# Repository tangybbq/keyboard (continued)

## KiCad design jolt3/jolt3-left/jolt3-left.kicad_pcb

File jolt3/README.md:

# The Jolt 3

The Jolt 2, with the varying-elevation design has turned out to be a rather nice keyboard to use.
However there are some challenges:

- Even with sockets, assembling all of the key risers is quite time consuming.  This makes it more
  challenging to experiment with the rest of the electronics.
- With more circuitry on the main board, the left/right distinction greatly increases the work to
  try a new design.

As such, the main goal of the Jolt 3 is to modularize the board design.  This is similar to using
existing rp2040 modules in the design, but in this case, the mezzanine board is my design instead,
with the following changes:

- Larger available area.  This allows me to put more on the board.
- Always have a debug headers.  The plethora of small boards that don't bother with debug headers is
  baffling to me.  I understand a lot of people are doing python, but this makes the board almost
  entirely useless for any serious development.

In order to make this board able to be used on either side of the keyboard, we'll need to avoid any
connectors that vary from side to side, notably the rj-45 (or whatever jack I decide on).  Now might
be a good time to try a different connector.  USB-C would work well for this, but it seems to be
hard to find thin USB-C cables.  I don't want 240W, I want a thin cable.  The old Apple cable is
really nice, but is getting harder and harder to find.  Another option is RJ-9.  The cables aren't
quite as available (and tend to be curly), but this might be a nice compromise.

Another thought, since I now have a tented stand, is to put the rj45 on the bottom side of the
board, and cut a notch for it.

It is fine to have the USB and debug header on the small board.

Sockets are going to be nice.  Regular pin header sockets are fine, but do lift the board up quite a
bit.  It still might end up being the best approach, as narrower pitch are harder to find.

This design should make some number of pins available in standard places:

- GPIOs for row and column.  4+6 is adequate for any of my current designs.  A two-row version with
  a single CPU would need 5+6, so 11 pins for this seems fine.
- Pins for the RJ-45?  If this is underneath, it gives more space.
- Battery.  The base board should be designed to allow a battery underneath.  The lines will just
  run directly to the small board.

## Dimensions

If we put the RJ-45 underneath, this gives us 41mm across by 39mm high.  It might make more sense to
just have the board be square at 40x40mm.

For a two-row design, this space could still be available.  It is unclear to me where my future
desire for 2-row will go (it depends on whether I become fully comfortable with steno+taipo).

## Design

The main boards will be jolt3-left, and jolt3-right, with the same connector on each.

- Supports the 7 risers in the same positioning and connection as the jolt2.
- Has a 40x40mm area for a mezzanine board.
- Defines a pinout for connections between the boards.  There are 20 pins needed, plus whatever is
  needed for extra grounding. A single row is likely to be fine.r
- Decide on the particular mezzanine connector to use.  It might make sense to have on one side with
  standoffs on the other sides.

The smallest M-2 size is 22x42, which would fit (but give half the available area.

I've ended up going for the [DF40C](https://www.hirose.com/product/p/CL0684-4010-9-51#) series of
connectors, 30 pin with a 3mm board spacing.  I could probably do 2mm, but the pins on the RJ-45 are
fairly long, and 3mm avoids the need to trim.  I'll use 3 1mm thick nylon washers for each standoff.

Rev A implements the following:

- jolt3-left: The left side.  The only components are the holes to mount the risers, the RJ-45, a
  place to mount the 2AA battery holder, and two pull up resistors for I2C.
- jolt3-right: The same as left, with minor changes: no pullups on I2C, Tx and Rx on the serial
  lines are swapped.
- jolt3-mez2040: The rp2040 circuitry on the mezzanine board.  I ended up with 38x38mm, to bring the
  mounting holes in enough on the main board to clear the stand.  The rp2040 is rotated 90 degrees
  to better route gpios to the connector (moves the crystal out of the way).
- Use the same riser boards "jolt2-verts" from the Jolt2.

The biggest change from previous designs is moving away from the Arm Cortex-M debug header to the
6-pin [Tag Connect](https://www.tag-connect.com/).  This requires no components on the board, just
some holes and pads, taking about the same area as the Cortex-M connector.  There is a smaller one,
but for these prototypes, the definitive connection seems better.  The cable is about $45 and should
last a long time.

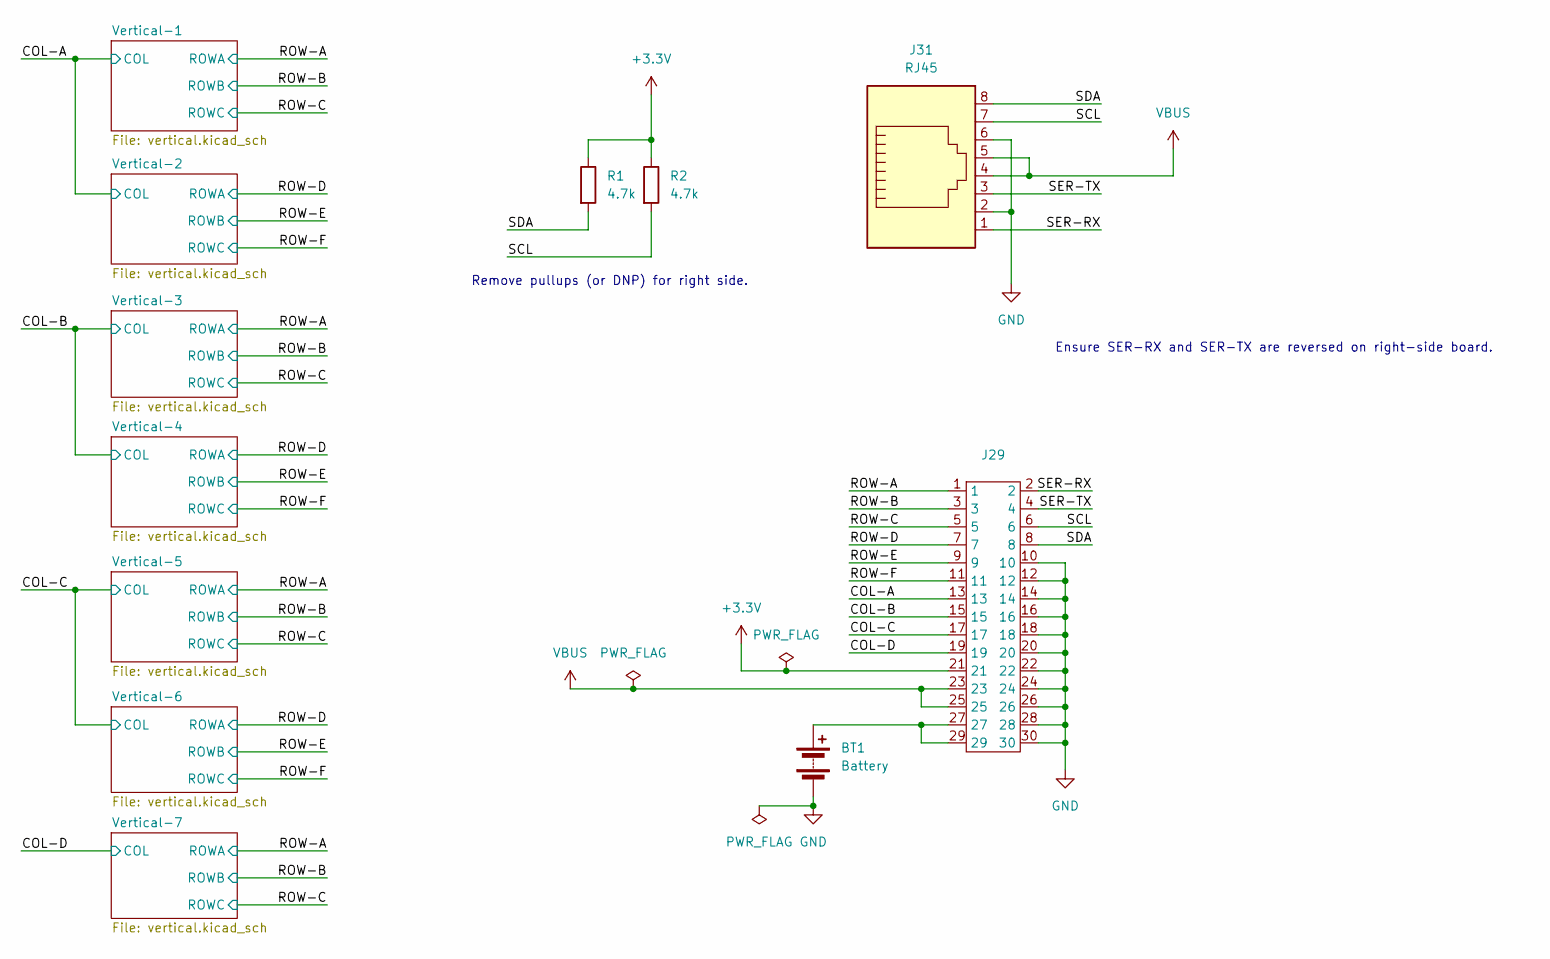
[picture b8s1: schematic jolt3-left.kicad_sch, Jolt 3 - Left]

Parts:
BT1: Battery; BAT-2xAA-SHELL-CASE-BOX
J29: df40c-2_0-30P-0_4v
J31: RJ45; RJ45_Amphenol_54602-x08_Horizontal
R1, R2: 4.7k; R_0603_1608Metric_Pad0.98x0.95mm_HandSolder

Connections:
+3.3V: J29.21, R1.1, R2.1
/COL-A: J29.13; also elsewhere on the board
/COL-B: J29.15; also elsewhere on the board
/COL-C: J29.17; also elsewhere on the board
/COL-D: J29.19; also elsewhere on the board
/ROW-A: J29.1; also elsewhere on the board
/ROW-B: J29.3; also elsewhere on the board
/ROW-C: J29.5; also elsewhere on the board
/ROW-D: J29.7; also elsewhere on the board
/ROW-E: J29.9; also elsewhere on the board
/ROW-F: J29.11; also elsewhere on the board
/SCL: J29.6, J31.7, R2.2
/SDA: J29.8, J31.8, R1.2
/SER-RX: J29.2, J31.1
/SER-TX: J29.4, J31.3
GND: BT1.2 (-), J29.10, J29.12, J29.14, J29.16, J29.18, J29.20, J29.22, J29.24, J29.26, J29.28, J29.30, J31.2, J31.6
unnamed: BT1.1 (+), J29.27, J29.29
VBUS: J29.23, J29.25, J31.4, J31.5

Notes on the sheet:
Ensure SER-RX and SER-TX are reversed on right-side board.
Remove pullups (or DNP) for right side.

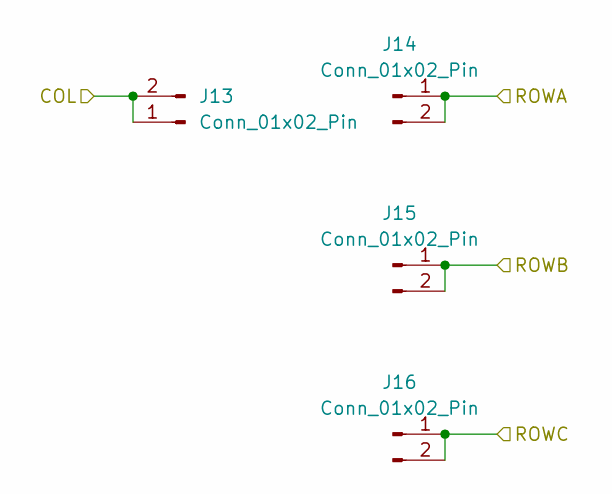
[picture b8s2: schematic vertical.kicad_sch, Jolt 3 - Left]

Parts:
J13, J14, J15, J16: Conn_01x02_Pin; PinHeader_1x02_P2.54mm_Vertical

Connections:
/COL-B: J13.1, J13.2; also elsewhere on the board
/ROW-D: J14.1, J14.2; also elsewhere on the board
/ROW-E: J15.1, J15.2; also elsewhere on the board
/ROW-F: J16.1, J16.2; also elsewhere on the board

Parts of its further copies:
J1, J2, J3, J4, J5, J6, J7, J8, J9, J10, J11, J12, J17, J18, J19, J20, J21, J22, J23, J24, J25, J26, J27, J28: Conn_01x02_Pin; PinHeader_1x02_P2.54mm_Vertical

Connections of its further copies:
/COL-A: J1.1, J1.2, J5.1, J5.2; also elsewhere on the board
/COL-B: J9.1, J9.2; also elsewhere on the board
/COL-C: J17.1, J17.2, J21.1, J21.2; also elsewhere on the board
/COL-D: J25.1, J25.2; also elsewhere on the board
/ROW-A: J2.1, J2.2, J10.1, J10.2, J18.1, J18.2, J26.1, J26.2; also elsewhere on the board
/ROW-B: J3.1, J3.2, J11.1, J11.2, J19.1, J19.2, J27.1, J27.2; also elsewhere on the board
/ROW-C: J4.1, J4.2, J12.1, J12.2, J20.1, J20.2, J28.1, J28.2; also elsewhere on the board
/ROW-D: J6.1, J6.2, J22.1, J22.2; also elsewhere on the board
/ROW-E: J7.1, J7.2, J23.1, J23.2; also elsewhere on the board
/ROW-F: J8.1, J8.2, J24.1, J24.2; also elsewhere on the board

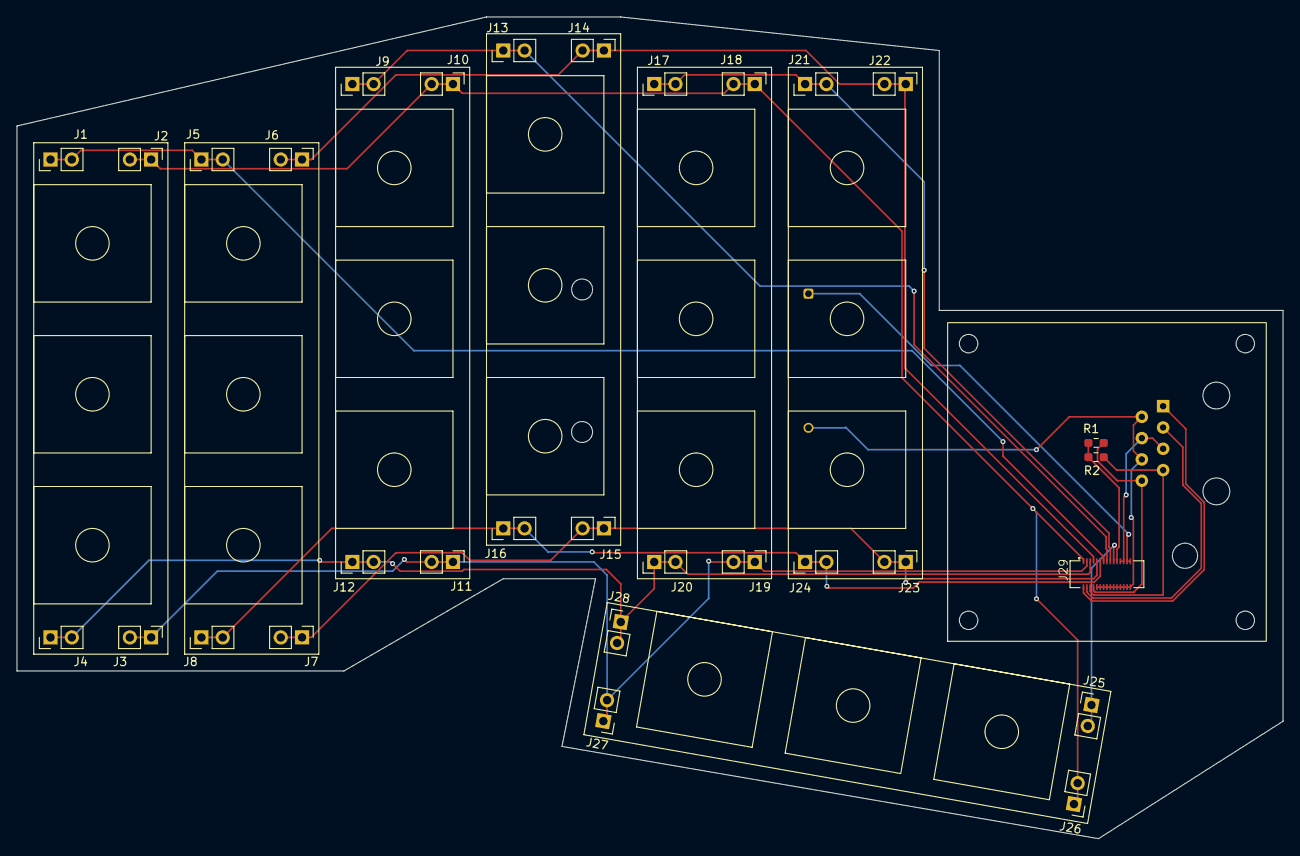
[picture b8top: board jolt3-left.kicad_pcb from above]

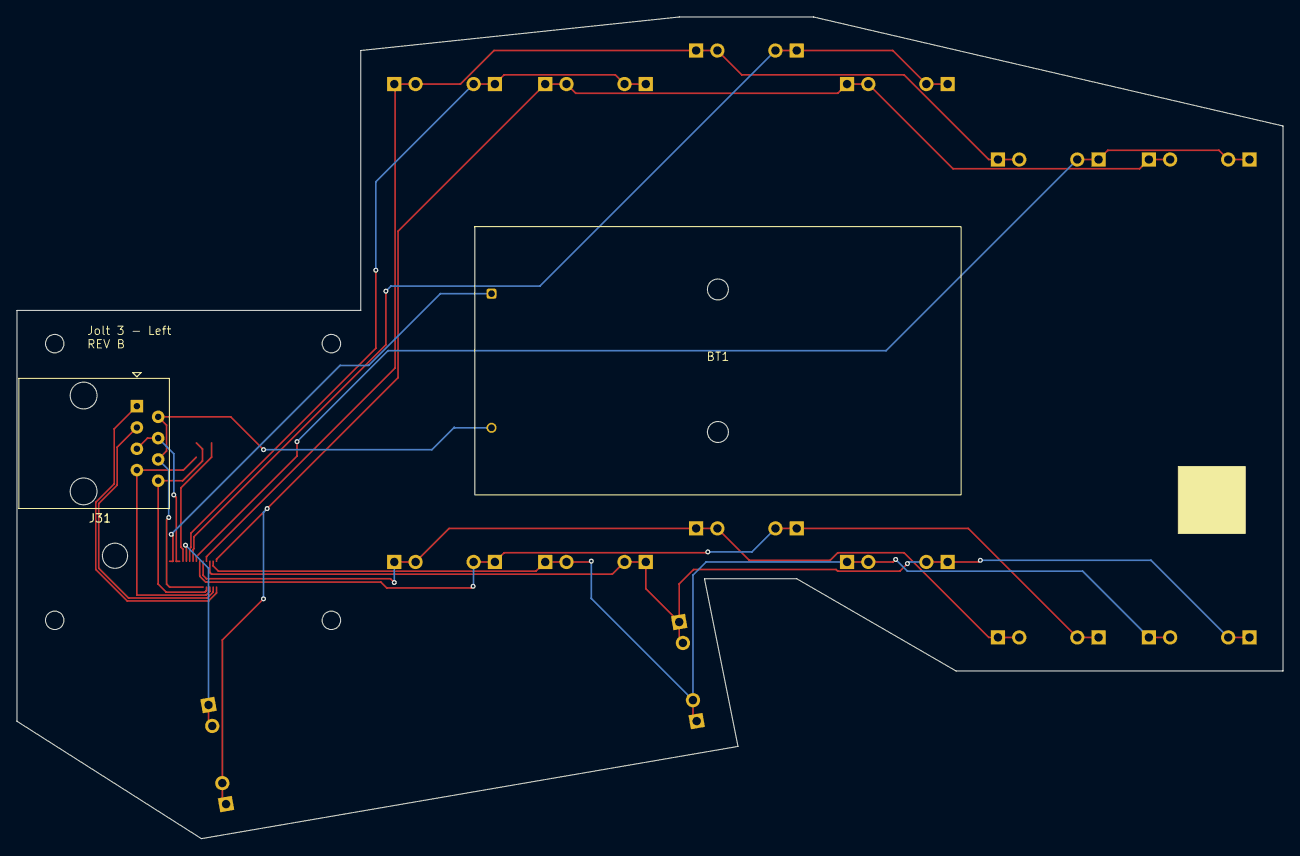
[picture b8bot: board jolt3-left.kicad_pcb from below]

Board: 2 copper layers, 151.0 x 98.0 mm, 33 parts (2 on the bottom side), 18 nets.

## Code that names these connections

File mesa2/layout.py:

#!/usr/bin/env python3
"""mesa2 key layout, derived from hand-scan-1.

Method:
  1. Mirror the right hand about the axis midway between the two hand centroids.
  2. Average it with the left hand, mark for mark. That is the "average of my
     measurements" and it forces a symmetric board; the unibody angle survives
     as the average of the two hands' rotations.
  3. Each finger column: centre = the rest mark (m2), axis = principal direction
     of its three marks, two keys at +/- rock/2 along that axis.
  4. Thumbs: two keys on the measured arc, centred on it, caps tangent.
  5. Emit the averaged hand and its mirror = 20 keys.

Frame is the measurement sheet's: +X right, +Y toward you.
"""
import math, json

ROCK = 17.0          # row pitch, fixed by the caps (16.5 + 0.5)
THUMB_PITCH = 18.0   # thumb pair separation along the arc

MARKS = {
 'L': {'pinky':  [(15.53,30.50),(29.27,35.07),(32.66,38.48)],
       'ring':   [(55.32,20.48),(55.68,29.34),(54.99,39.07)],
       'middle': [(73.99,20.13),(73.63,28.25),(73.54,40.11)],
       'index':  [(99.18,44.48),(92.72,50.59),(86.81,59.81)],
       'thumb':  [(84.47,85.49),(96.94,94.97),(109.96,110.62)]},
 'R': {'pinky':  [(214.03,21.51),(202.06,29.35),(198.54,34.01)],
       'ring':   [(172.58,17.69),(173.37,24.63),(173.81,35.69)],
       'middle': [(147.31,20.32),(150.60,26.34),(154.55,35.57)],
       'index':  [(132.93,41.01),(140.21,50.14),(145.28,58.50)],
       'thumb':  [(147.08,83.95),(135.69,91.23),(123.95,110.32)]},
}
FINGERS = ['pinky','ring','middle','index']

def centroid(h):
    pts=[p for f in h.values() for p in f]
    return (sum(p[0] for p in pts)/len(pts), sum(p[1] for p in pts)/len(pts))

cL, cR = centroid(MARKS['L']), centroid(MARKS['R'])
AXIS = (cL[0]+cR[0])/2
print(f"left centroid  ({cL[0]:7.2f}, {cL[1]:6.2f})")
print(f"right centroid ({cR[0]:7.2f}, {cR[1]:6.2f})   dy {cR[1]-cL[1]:+.2f} mm")
print(f"mirror axis x = {AXIS:.2f}\n")

# mirror the right hand into left-hand coordinates, then average mark for mark
avg={}
for f in FINGERS+['thumb']:
    avg[f]=[((l[0]+(2*AXIS-r[0]))/2, (l[1]+r[1])/2)
            for l,r in zip(MARKS['L'][f], MARKS['R'][f])]

def axis_angle(pts):
    """principal direction, degrees from +Y (away from you); + leans toward +X"""
    n=len(pts); mx=sum(p[0] for p in pts)/n; my=sum(p[1] for p in pts)/n
    sxx=sum((p[0]-mx)**2 for p in pts); syy=sum((p[1]-my)**2 for p in pts)
    sxy=sum((p[0]-mx)*(p[1]-my) for p in pts)
    th=0.5*math.atan2(2*sxy, sxx-syy)
    vx,vy=math.cos(th),math.sin(th)
    if vy<0: vx,vy=-vx,-vy
    return math.degrees(math.atan2(vx,vy))

print("averaged hand, per finger (L/R disagreement = spread between the two hands):")
cols={}
for f in FINGERS:
    a = axis_angle(avg[f])
    aL, aR = axis_angle(MARKS['L'][f]), -axis_angle(MARKS['R'][f])
    if f=='pinky':
        # the pinky is an elbow, not a line: use the chord through the extremes
        m1,m3 = avg[f][0], avg[f][2]
        a = math.degrees(math.atan2(m1[0]-m3[0], m1[1]-m3[1]))
        if a>90: a-=180
        if a<-90: a+=180
    cols[f]=(avg[f][1], a)                      # centre = rest mark, plus axis
    print(f"  {f:7s} centre ({avg[f][1][0]:7.2f},{avg[f][1][1]:6.2f})  axis {a:+6.1f} deg"
          f"   (L {aL:+6.1f} / R-mirrored {aR:+6.1f}, spread {abs(aL-aR):4.1f})")

print("\nspreads and staggers between averaged column centres (outer -> inner):")
for a,b in zip(FINGERS, FINGERS[1:]):
    pa,pb = cols[a][0], cols[b][0]
    print(f"  {a:6s} -> {b:6s}  dx {pb[0]-pa[0]:+7.2f}  dy {pb[1]-pa[1]:+7.2f}")

json.dump({'axis':AXIS,'avg':{k:[list(p) for p in v] for k,v in avg.items()},
           'cols':{k:[list(v[0]),v[1]] for k,v in cols.items()}}, open('layout.json','w'), indent=1)

# ---------------------------------------------------------------- placement --
# Matrix -> finger, from the netlist. Left COL_A..D = pinky..index; right is
# mirror-ordered COL_A..D = index..pinky, which makes each finger carry the same
# key pair on both hands (pinky R/A, ring S/O, middle N/T, index I/E).
FAR  = {'pinky':'R','ring':'S','middle':'N','index':'I'}   # ROW_A / ROW_C
NEAR = {'pinky':'A','ring':'O','middle':'T','index':'E'}   # ROW_B / ROW_D
THUMB_OUTER = {'L':'SP','R':'BK'}      # LSP sits at mesa1's outer thumb today
THUMB_INNER = {'L':'BK','R':'SP'}

ORIGIN_X, ORIGIN_Y = 150.0, 34.0       # mirror axis / far-row datum on the board

def unit(a):
    r=math.radians(a); return (math.sin(r), math.cos(r))   # +Y-ward, leans to +X

# Minimum outward nudge per column so no two caps come closer than 0.5 mm.
# Angles and staggers are left exactly as measured; only the outward spacing
# moves, and only as far as the caps demand.
NUDGE = {'pinky':1.7,'ring':0.5,'middle':0.1,'index':0.1}

keys={}
for f in FINGERS:
    (cx,cy), a = cols[f]
    cx -= NUDGE[f]
    ux,uy = unit(a)
    keys[(f,'far')]  = (cx-ux*ROCK/2, cy-uy*ROCK/2, a)
    keys[(f,'near')] = (cx+ux*ROCK/2, cy+uy*ROCK/2, a)

# thumbs: two keys on the measured arc, centred, caps across the travel
t = avg['thumb']
mid = ((t[0][0]+t[2][0])/2, (t[0][1]+t[2][1])/2)
chord = math.degrees(math.atan2(-(t[2][1]-t[0][1]), t[2][0]-t[0][0]))   # CCW from +X, screen
hx = math.cos(math.radians(chord)); hy = -math.sin(math.radians(chord))
keys[('thumb','outer')] = (mid[0]-hx*THUMB_PITCH/2, mid[1]-hy*THUMB_PITCH/2, chord+90)
keys[('thumb','inner')] = (mid[0]+hx*THUMB_PITCH/2, mid[1]+hy*THUMB_PITCH/2, chord+90)
print(f"\nthumb arc: chord {math.dist(t[0],t[2]):.2f} mm at {chord:+.1f} deg from +X;"
      f" pair {THUMB_PITCH} mm apart, caps across the travel")

def norm(a):                       # socket may sit at a or a+180; pick nearest 0
    while a >  90: a -= 180
    while a <= -90: a += 180
    return a

# The hand separation is already in the measurement: both hands were marked on
# one sheet, so AXIS (midway between the two centroids) is the real mirror line.
# Translate that to the board rather than inventing a margin.
ys=[v[1] for v in keys.values()]
sx, sy = ORIGIN_X - AXIS, ORIGIN_Y - min(ys)

place={}
for (f,which),(x,y,a) in keys.items():
    if f=='thumb':
        nm = THUMB_OUTER if which=='outer' else THUMB_INNER
        lref, rref = f'SW_L{nm["L"]}1', f'SW_R{nm["R"]}1'
    else:
        k = FAR[f] if which=='far' else NEAR[f]
        lref, rref = f'SW_L{k}1', f'SW_R{k}1'
    X, Y = x+sx, y+sy
    place[lref] = (X, Y, norm(a))
    place[rref] = (2*ORIGIN_X-X, Y, norm(-a))

print(f"\n{'ref':9s} {'x':>8s} {'y':>8s} {'rot':>7s}   finger / row")
lbl={v:k for k,v in [((f,w),(f,w)) for f,w in keys]}
for (f,which) in sorted(keys, key=lambda k:(FINGERS+['thumb']).index(k[0])):
    for hand in 'LR':
        if f=='thumb':
            nm=(THUMB_OUTER if which=='outer' else THUMB_INNER)[hand]
            ref=f'SW_{hand}{nm}1'
        else:
            ref=f'SW_{hand}{(FAR if which=="far" else NEAR)[f]}1'
        X,Y,R = place[ref]
        print(f"{ref:9s} {X:8.2f} {Y:8.2f} {R:+7.1f}   {f} / {which}")
json.dump(place, open('placement.json','w'), indent=1)
print(f"\nkey field: x {min(v[0] for v in place.values()):.1f}..{max(v[0] for v in place.values()):.1f}"
      f"  y {min(v[1] for v in place.values()):.1f}..{max(v[1] for v in place.values()):.1f}"
      f"   ({max(v[0] for v in place.values())-min(v[0] for v in place.values()):.1f}"
      f" x {max(v[1] for v in place.values())-min(v[1] for v in place.values()):.1f} mm)")

# ------------------------------------------------------- keycap clearance ----
CAP=(17.5,16.5)
def corners(cx,cy,th):
    w,h=CAP; a=math.radians(th); c,s_=math.cos(a),math.sin(a)
    return [(cx+dx*c+dy*s_, cy-dx*s_+dy*c) for dx,dy in
            [(-w/2,-h/2),(w/2,-h/2),(w/2,h/2),(-w/2,h/2)]]
def gap(A,B):
    best=-1e9
    for poly in (A,B):
        for i in range(4):
            x1,y1=poly[i]; x2,y2=poly[(i+1)%4]
            nx,ny=-(y2-y1),(x2-x1); L=math.hypot(nx,ny); nx,ny=nx/L,ny/L
            pa=[p[0]*nx+p[1]*ny for p in A]; pb=[p[0]*nx+p[1]*ny for p in B]
            best=max(best,max(min(pb)-max(pa),min(pa)-max(pb)))
    return best
import itertools
caps={r:corners(*v) for r,v in place.items()}
bad=[]
for (ra,A),(rb,B) in itertools.combinations(caps.items(),2):
    g=gap(A,B)
    if g < 0.5: bad.append((g,ra,rb))
bad.sort()
print(f"\nkeycap clearance ({len(caps)} caps, {len(caps)*(len(caps)-1)//2} pairs), "
      f"anything under 0.50 mm:")
if not bad: print("   all clear")
for g,ra,rb in bad[:14]:
    print(f"   {g:+6.2f} mm  {ra} / {rb}" + ("   *** OVERLAP ***" if g<0 else ""))

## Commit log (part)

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2022-10-30 Create initial proto2 with images
2022-10-30 Fix images to show inline
2022-10-30 Include firmware reference.
2022-10-30 Add design files for the proto2
2022-11-15 Update README for the proto3
2022-11-15 Add design files for proto3
2024-02-23 Add initial qwerty diagram
2024-02-23 Add qwerty diagram
    This describes my layout for the 3-row keyboard qwerty mode. There are
    lots of combos, which works well, as the keys are designed to be pressed
    this way. There are also three layers for numbers, navigation, and
    function keys.
    The number layer also adds keys for hex, with 'e' in a weird place,
    because the regular 'e' key is taken by a '3'.
2024-12-06 Add my footprint and symbol libraries
2024-12-06 Add bletest project
2024-12-07 Full routing done
    There are still a bunch of ERC violations.
2024-12-07 Clean up most ERC violations
    The remaining are silkscreen overlaps or clipping issues.
2024-12-16 jolt2: Add Initial WIP
    The jolt is a "3D" staggered keyboard. There are 3 PCB designs here:
    - jolt2-verts: These are the 1x3 individual key segments. Each holds
    3 keys and is a vertical column.
    - jolt2-left: The base of the left side of the keyboard. This is the
    side intended to be plugged into the host.
    - jolt2-right (not yet made): The right side base.
2024-12-16 shield-kb1: A keyboard prototype shield for the nRF DK boards
    This initial one has 4 keys, connectors for compatibility with left and
    right, and some LEDs.
2024-12-16 Cleanup the Cortex-M Debug footprint
    Try to make a silkscreen for it that shows the full connector, with a
    clear pin 1 indicator, that also doesn't overlap any pads.
2024-12-16 Commit some missing footprints
    The RP2040 comes from their reference schematic.
    The AP211-SO8 and QBLP600-RGB5 I've drawn from the datasheets.
2024-12-16 jolt2: Prepare rev A
    This is Rev A, being sent for production.
2024-12-16 Rev A of bletest
    Finish cleanup, and remove last remaining violations.
    There are a handful of silkscreen overlaps with explicit exclusions.
2024-12-16 shield-kb1: rev-b updates: LEDs
    In addition to actually hooking up the switches, add a PWM RGB LED. It
    is hard to find these that will work with 3.2V, hopefully this one will.
    It is fairly small, and I've come up with some resistors for about 15mA.
    I've also added a jumper to allow the SK6812 to be powered either from
    3.3V or 5V, which should help figring out issues with that.
2024-12-16 bletest-2: Minor layer visibility change
2024-12-16 jolt2-tiny204-left: Cleanup and route
    Fix the designators for all of the pin headers. This was mostly done
    manually, naming them consistently for each component.
    Perform manual routing.
    This should be ready for REV A.
2024-12-16 Remove some stray committed files
2024-12-16 jolt2: add pim-left board
    Copy the current left board, to jolt2-pim-left, which will be
    re-designed using the PIM722, the Pimoroni 25.4mm x 25.4mm PGA board.
2024-12-16 Create jolt2-tiny2040-left
    The jump references are messed up, and I'm going to edit the text file
    directly to fix them.
2024-12-16 jolt2-pim-left: Finalize routing
2024-12-16 bletest-2: Remove xls bom
2024-12-16 bletest-2: update xls bom
    This file is not actually useful, as the html bom from the KiCad plugin
    is much more useful.
2024-12-16 jolt-tiny2040-right: Create and build rev A
    Create the right side, copying the left, and flipping everything. Route
    the result, ready for Rev A production.
2024-12-16 jolt2-pim-left: Add uart terminating resistors
    Place 27 ohm series resisters on the inter-board uart lines.
2024-12-16 jolt2-left: Add inter-board termination
    Add 27 ohm resisters for termination on the inter-board protocol.
2024-12-16 README: Update with the new KiCad designs
2024-12-16 Rename jolt-tiny2040-right to jolt2-tiny2040-right
    Fix the name to align with the rest of the PCBs.
2024-12-17 Copy jolt2-tiny2040-left to jolt2-pm2350-left
    Start on the 2350 PCB by copying the tiny2040.
2024-12-17 jolt2: Update pm2350 left footprint
    Build the footprint, updating it for the left side of the keyboard
2024-12-24 jolt2-tiny2040-right: Update PCB from schematic
    Schematic was missing swapping TX and RX.
2025-01-04 Various PCB updates
    This is before fixing the footprint for the WS2812. Turns out there is a
    ws2812 MINI, and a MINI-HS, and they have very different footprints.
2025-01-04 jolt2-left: Fix symbol and footprint for ws2812
    The ws2812 has both a MINI and a MINI-HS footprint, and they have rather
    different footprints. Update the symbol and draw a footprint for the
    proper one we have purchased.
2025-01-04 Add assembly instructions for the jolt2
    Write up some basic instructions with photos.
2025-01-14 jolt2-left: Add some calibration circles
    Add some calibration circles to a user layer that can be included in a
    CAD export and should help determining the position of the keys.
2025-01-22 jolt3: First pass
    This defines a mezzanine board, with connector, and separate left and
    right sides.
    This design doesn't work with the right side, as the connector
    interferes with the RJ-45, so I have to position that differently.
2025-01-22 Jolt 3: Rev A for 3 boards
    Send Rev A out for jolt3-left, jolt3-right, and j3-mez-2040.
2025-01-24 Update the Jolt3 Readme
2025-01-24 Jolt3 RevA updated ibom files
    Update the jolt3 ibom files for the Rev A sent to manufacturing.
2025-01-24 Jolt 3: Add notes about the Tag-Connect
    The jolt3 moves away from the Cortex-M debug header to the Tag-Connect,
    saving money and assembly work per board, at the cost of a single $45
    cable.
2026-04-19 Update for latest KiCad
    This seems to have done a rewrite of uuids within the files.
